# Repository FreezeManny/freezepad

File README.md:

# Freezepad

This repository contains all files and configuration for the **Freezepad**, a custom wireless 20-key (5×4) low-profile macropad built completely from scratch. The goal was to create the smallest possible macropad footprint — achieved by placing the Nice!Nano v2 controller directly below the switches and eliminating diodes entirely. It runs ZMK firmware and is housed in a custom 3D printed case.

## Table of Contents

- [Hardware Components](#hardware-components)
- [PCB](#pcb)
- [Firmware (ZMK)](#firmware-zmk)
- [3D Printed Case](#3d-printed-case)
- [Build Notes](#build-notes)

---

## Hardware Components

| Component | Item | Notes |
| :--- | :--- | :--- |
| **PCB** | Custom Freezepad PCB | Ordered from JLCPCB. Files in `/pcb/`. |
| **Small Electronics** | 1x Push Button 6x2mm, 20x Kailh Choc V1 Hotswap Sockets, 1x Battery Switch | Ordered from AliExpress. |
| **Small Case Parts** | 3x M3 Heat Insert, 3x M3 Screw | For securing the PCB to the case. |
| **Controller** | 1x Nice!Nano v2 (or compatible) | Wireless connectivity via Bluetooth. |
| **Battery** | 1x 102050 LiPo (1000mAh) | Fits in the custom case. |
| **Switches** | 20x Kailh Choc V1 | e.g., Sunset, Robins. |
| **Keycaps** | 20x Choc V1 Keycaps | e.g., MBK Blank Choc Keycaps. |
| **Case** | Custom 3D Printed Case | Files are located in the `/case` directory. |

---

## PCB

The custom PCB was designed using Ergogen. The files are located in the `/pcb/` directory.

---

## Firmware (ZMK)

The Freezepad runs on [ZMK Firmware](https://zmk.dev/docs), designed for wireless keyboards and macropads.

### Configuration

* **ZMK Config:** The main configuration files are located in the `/config/` directory.

### Configure, Build & Flash

* **Configuration:** Use the [Keymap Editor](https://nickcoutsos.github.io/keymap-editor/)
* **Build:** Standard GitHub Actions (see `build.yaml`)
* **Flash:** Consult the [Nice!Nano documentation](https://nicekeyboards.com/docs/nice-nano/)

---

## 3D Printed Case

A custom case designed in Fusion360. Source and STEP files are provided in `/case`.

### Recommended Print Settings

* **Material:** ABS / ASA / PETG preferred for better heat resistance
* **Outer Walls:** Minimum of 3
* **Layer Height:** 0.2mm
* **Infill:** 15–20%
* **Supports:** Not required

---

## Build Notes
* **ControllerPlacement:** The Controller sits under the switches. Ensure that you trim the soldered Pins flush, otherwise swtiches will not plug in flush.
* **Battery Switch:** The battery switch is mounted on the PCB and accessible from the side of the case.

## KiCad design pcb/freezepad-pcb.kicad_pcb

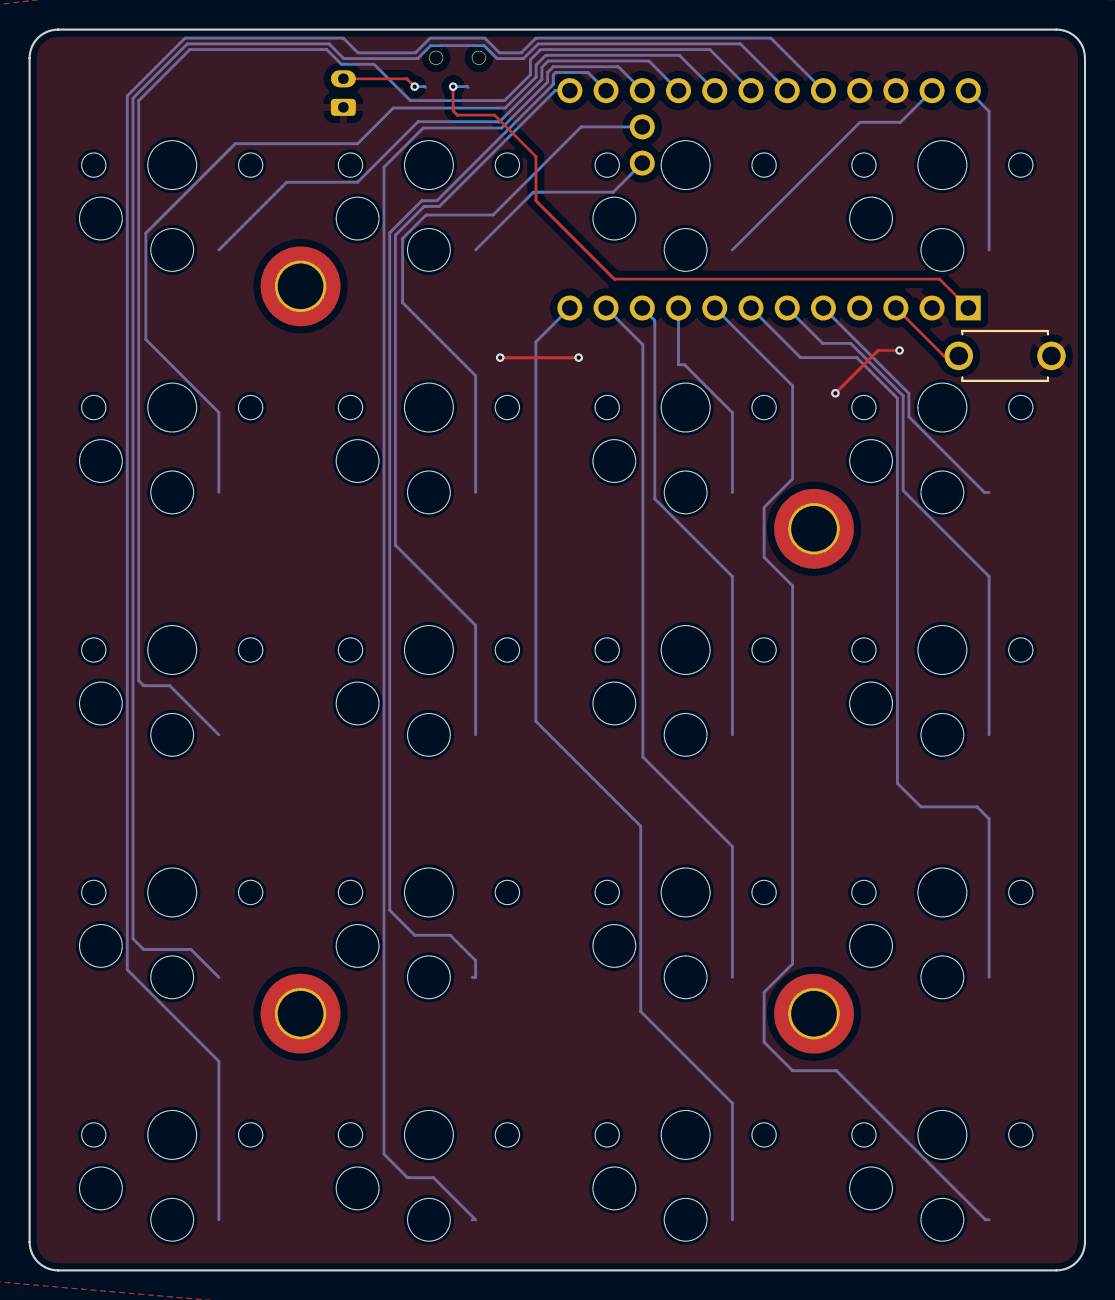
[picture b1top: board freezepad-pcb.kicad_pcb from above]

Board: 2 copper layers, 74.0 x 87.0 mm, 24 parts (1 on the bottom side), 24 nets.

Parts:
B1: ResetSW
JST1: battery_connector_jst_ph_2
MCU1: ProMicro
S1, S2, S3, S4, S5, S6, S7, S8, S9, S10, S11, S12, S13, S14, S15, S16, S17, S18, S19, S20: PG1350
T1: SPDT_C128955

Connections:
B+: JST1.2, T1.1
GND: B1.2, JST1.1, MCU1.2, MCU1.15, MCU1.16, S1.2, S2.2, S3.2, S4.2, S5.2, S6.2, S7.2, S8.2, S9.2, S10.2, S11.2, S12.2, S13.2, S14.2, S15.2, S16.2, S17.2, S18.2, S19.2, S20.2
RAW: MCU1.1, T1.2
RST: B1.1, MCU1.3
matrix_col1_row1: MCU1.17, S1.1
matrix_col1_row2: MCU1.18, S2.1
matrix_col1_row3: MCU1.19, S3.1
matrix_col1_row4: MCU1.20, S4.1
matrix_col1_row5: MCU1.21, S5.1
matrix_col2_row1: MCU1.22, S6.1
matrix_col2_row2: MCU1.23, S7.1
matrix_col2_row3: MCU1.24, S8.1
matrix_col2_row4: MCU1.31, S9.1
matrix_col2_row5: MCU1.32, S10.1
matrix_col3_row1: MCU1.12, S11.1
matrix_col3_row2: MCU1.11, S12.1
matrix_col3_row3: MCU1.10, S13.1
matrix_col3_row4: MCU1.9, S14.1
matrix_col3_row5: MCU1.14, S15.1
matrix_col4_row1: MCU1.8, S16.1
matrix_col4_row2: MCU1.7, S17.1
matrix_col4_row3: MCU1.6, S18.1
matrix_col4_row4: MCU1.5, S19.1
matrix_col4_row5: MCU1.13, S20.1

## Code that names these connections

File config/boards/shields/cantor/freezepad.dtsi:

#include <dt-bindings/zmk/matrix_transform.h>
#include "freezepad-layouts.dtsi"
&physical_layout0 {
    transform = <&default_transform>;
};

// Keyscan Setup
/ {
    chosen {
        zmk,kscan = &kscan0;
        zmk,physical-layout = &physical_layout0;
    };

    default_transform: keymap_transform_0 {
        compatible = "zmk,matrix-transform";
        columns = <4>;
        rows = <5>;

// | SW00 | SW01 | SW02 | SW03 |
// | SW10 | SW11 | SW12 | SW13 |
// | SW20 | SW21 | SW22 | SW23 |
// | SW30 | SW31 | SW32 | SW33 |
// | SW40 | SW41 | SW42 | SW43 |

        map = <
            RC(0,0)  RC(0,1)  RC(0,2)  RC(0,3)
            RC(1,0)  RC(1,1)  RC(1,2)  RC(1,3)
            RC(2,0)  RC(2,1)  RC(2,2)  RC(2,3)
            RC(3,0)  RC(3,1)  RC(3,2)  RC(3,3)
            RC(4,0)  RC(4,1)  RC(4,2)  RC(4,3)
        >;
    };

    kscan0: kscan {
        compatible = "zmk,kscan-gpio-direct";
        label = "KSCAN";
        wakeup-source;
        input-gpios =
            <&gpio0 2  (GPIO_ACTIVE_LOW | GPIO_PULL_UP)>, //matrix_col1_row1 - P2
            <&gpio0 7  (GPIO_ACTIVE_LOW | GPIO_PULL_UP)>, //matrix_col2_row1 - P7
            <&gpio0 10 (GPIO_ACTIVE_LOW | GPIO_PULL_UP)>, //matrix_col3_row1 - P10
            <&gpio0 18 (GPIO_ACTIVE_LOW | GPIO_PULL_UP)>, //matrix_col4_row1 - P18

            <&gpio0 3  (GPIO_ACTIVE_LOW | GPIO_PULL_UP)>, //matrix_col1_row2 - P3
            <&gpio0 8  (GPIO_ACTIVE_LOW | GPIO_PULL_UP)>, //matrix_col2_row2 - P8
            <&gpio0 16 (GPIO_ACTIVE_LOW | GPIO_PULL_UP)>, //matrix_col3_row2 - P16
            <&gpio0 19 (GPIO_ACTIVE_LOW | GPIO_PULL_UP)>, //matrix_col4_row2 - P19

            <&gpio0 4  (GPIO_ACTIVE_LOW | GPIO_PULL_UP)>, //matrix_col1_row3 - P4
            <&gpio0 9  (GPIO_ACTIVE_LOW | GPIO_PULL_UP)>, //matrix_col2_row3 - P9
            <&gpio0 14 (GPIO_ACTIVE_LOW | GPIO_PULL_UP)>, //matrix_col3_row3 - P14
            <&gpio0 20 (GPIO_ACTIVE_LOW | GPIO_PULL_UP)>, //matrix_col4_row3 - P20

            <&gpio0 5  (GPIO_ACTIVE_LOW | GPIO_PULL_UP)>, //matrix_col1_row4 - P5
            <&gpio1 31 (GPIO_ACTIVE_LOW | GPIO_PULL_UP)>, //matrix_col2_row4 - P31
            <&gpio0 15 (GPIO_ACTIVE_LOW | GPIO_PULL_UP)>, //matrix_col3_row4 - P15
            <&gpio0 21 (GPIO_ACTIVE_LOW | GPIO_PULL_UP)>, //matrix_col4_row4 - P21

            <&gpio0 6  (GPIO_ACTIVE_LOW | GPIO_PULL_UP)>, //matrix_col1_row5 - P6
            <&gpio1 32 (GPIO_ACTIVE_LOW | GPIO_PULL_UP)>, //matrix_col2_row5 - P32
            <&gpio0 0  (GPIO_ACTIVE_LOW | GPIO_PULL_UP)>, //matrix_col3_row5 - P0
            <&gpio0 1  (GPIO_ACTIVE_LOW | GPIO_PULL_UP)>; //matrix_col4_row5 - P1
    };

};

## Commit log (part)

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2026-02-02 added simple config
2026-02-02 rename
2026-02-02 Improvements, Outlines Showed
2026-02-03 Added Footprints
2026-02-03 Working Example
2026-02-03 Rename PCB configuration to freezepad-pcb and set template to kicad8
2026-02-03 Added 5x4 Layout
2026-02-03 Refactor PCB configuration and remove Nice!Nano footprint
    - Updated the PCB configuration in freezepad-egrogen.yaml:
    - Added anchor shift for matrix centering.
    - Changed controller reference from 'ceoloide/mcu_nice_nano' to 'nicenano'.
    - Adjusted pin mappings for the controller to align with new configuration.
    - Removed unnecessary pin assignments for row 5.
    - Updated reset button component reference.
2026-02-03 Everything on right side except microcontroller
2026-02-03 Reversable Nice Nano
2026-02-03 Fixed Orientation
2026-02-03 Improved Sorting of nicenano, added proper position for things
2026-02-03 First sketch of updated Pin Mapping
2026-02-03 Added first layouted PCB
2026-02-03 Added Routing
2026-02-06 Add .gitignore for KiCad project files and temporary files
2026-02-06 Add initial KiCad project file for Freezepad PCB design
    - Created freezepad-pcb.kicad_pro with default design settings
    - Configured design rules, dimensions, and layer settings
    - Established net settings and IPC2581 metadata
    - Included teardrop and tuning pattern settings for enhanced routing
2026-02-06 Moved and removed Text Added ZMK
2026-02-06 feat: add Freezepad keyboard configuration and layout
    - Removed the existing 'the_abyss.yml' configuration file.
    - Added GitHub Actions workflow for building ZMK firmware.
    - Created build.yaml for GitHub Actions matrix configuration.
    - Introduced Kconfig.defconfig for Freezepad keyboard name.
    - Added freezepad-layouts.dtsi for physical layout definitions.
    - Created freezepad.conf for Freezepad configuration settings.
2026-02-06 feat: restructure Freezepad configuration files and layouts
2026-02-06 Initial Keymap
2026-02-06 Removed and added Transient
2026-02-06 feat: add SHIELD_FREEZEPAD configuration for Freezepad
2026-02-06 New Module standard test
2026-02-19 feat: update keymap bindings for FlightSim layer and adjust PCB step file pathu
2026-02-19 Bugfix
2026-02-19 Fixed layout
2026-02-19 Test Reupload
2026-02-19 Layout fix opus
2026-02-19 Used Cantor GPIOs to freezepad
2026-02-19 Added one more line
2026-02-19 Updated keymap
2026-02-19 Tried fix for Pin 102
2026-02-19 Fixed x key
2026-02-19 Reload, believe hw is broken
2026-02-19 Fixed X to B
2026-02-19 Added Back num Blocks
2026-02-19 Updated freezepad.keymap
2026-02-19 Added Screenshot
2026-02-23 feat: added README with Placeholder Photos
2026-02-23 Added Numpad Number 0 on additional layer
2026-02-25 AI comit for dongle
2026-02-26 Added Images
2026-02-26 Added Controller note
2026-02-26 Added Case files
2026-02-26 Updated Settings
2026-02-26 Added proper numblock numbering
2026-03-26 Add GNU General Public License v3
2026-05-18 removed dongle build
2026-06-22 restored dongle builds
2026-06-23 added dual build
